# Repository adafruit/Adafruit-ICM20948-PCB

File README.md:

## Adafruit ICM20948 9-DoF IMU PCB

<a href="http://www.adafruit.com/products/4554"><br/>
Click here to purchase one from the Adafruit shop</a>

PCB files for the Adafruit ICM20948 9-DoF IMU. 

Format is EagleCAD schematic and board layout
* https://www.adafruit.com/product/4554

### Description
When you want to sense orientation using inertial measurements, you need an Inertial Measurement Unit, and when it comes to IMUs, the more DoFs, the better! The ICM20948 from Invensense packs 9 Degrees of freedom into a teeny package, making it a one stop shop for all the DOFs you need! Within it’s svelte 3x3mm package there are not just one MEMS sensor die like your common sensors, but two sensor dies! The ICM20948 pair’s Invensense’s MEMS 3-axis accelerometer and gyro with the AK09916 3-axis magnetometer from Asahi Kasei Microdevices Corporation.

 All 9 axes of measurement are made available thanks to a crew of 16-bit Analog to Digital Converters, diligently converting the raw analog signals from the MEMs sensors to digital readings that are accessed via I2C or SPI. Each of the sensors have the quality specs you would expect from such a sensor. Just see what the datasheet has to say:

• 3-Axis Gyroscope with Programmable FSR of ±250 dps, ±500 dps, ±1000 dps, and ±2000 dps

• 3-Axis Accelerometer with Programmable FSR of ±2g, ±4g, ±8g, and ±16g

• 3-Axis Compass with a wide range to ±4900 µT

Now that’s a handy and capable team of sensors, ready to help orient your project in the right direction!

Like any high performance device the ICM20948 can a bit particular about how it needs to be worked with. Unlike the pick and place machines that normally handle these sensors, most of us humans can’t readily take a little guy like the ICM20948 and plop it into our circuit; it’s small! What’s more, the ICM20948 runs on 1.8V which is increasingly common for device manufacturers but isn’t hardly common for makers, learners, prototypers or the like. With that in mind, we’ve put the ICM20948 on a breakout with a 1.8V voltage regulator as well as level shifting circuitry to allow your 3.3V device such as a Feather M4 or Raspberry Pi, or a 5V device such as the Arduino Uno.

To make connections easy, our breakout puts makes the pins of the ICM20948 available on standard 0.100”/ 2.54mm pitch headers for use with a breadboard. Should you wish to avoid soldering, the Stemma QT form factor breakout also includes our Stemma QT connectors which just like the SparkFun Qwiic connectors they’re inspired by (and compatible with). Using these handy connectors you can simply plug in the sensor and get rolling with your project. You can even use them to daisy chain multiple sensors together! All of this is explained with wiring diagrams for use with Arduino or CircuitPython on the pages to come.

Lastly, all the wiring in the world wouldn’t do you much good if you didn’t know how to use those wires to talk to your sensor, so we’ve done the work of writing libraries for Arduino and CircuitPython that will allow you to use the ICM20948 with your favorite development board, be it an Arduino, Feather, Raspberry Pi, or one of the many other Arduino and CircuitPython compatible boards.

### License

Adafruit invests time and resources providing this open source design, please support Adafruit and open-source hardware by purchasing products from [Adafruit](https://www.adafruit.com)!

Designed by Limor Fried/Ladyada for Adafruit Industries.

Creative Commons Attribution/Share-Alike, all text above must be included in any redistribution. 
See license.txt for additional details.

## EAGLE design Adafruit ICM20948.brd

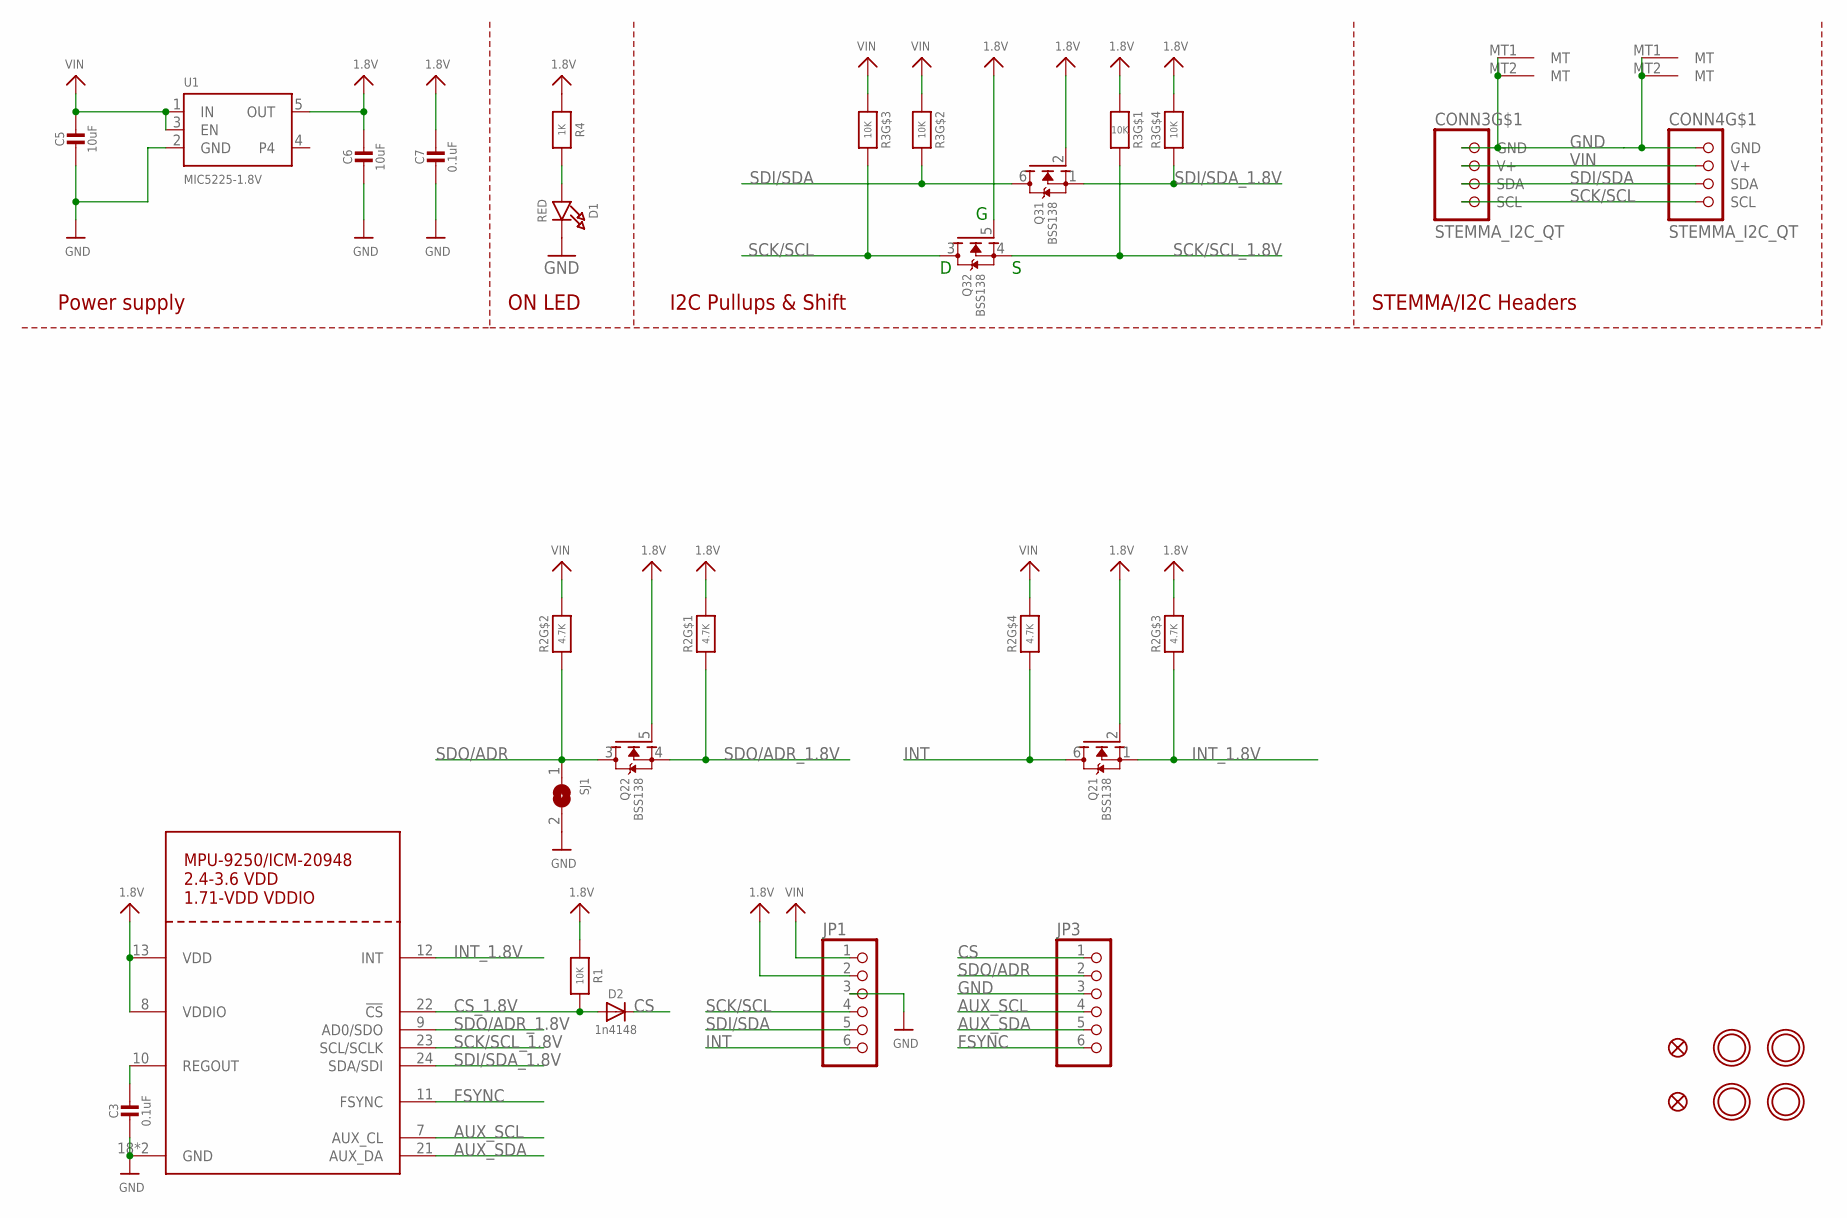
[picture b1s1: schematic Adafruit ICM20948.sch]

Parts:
C3, C7: 0.1uF; 0603-NO
C5, C6: 10uF; 0805-NO
CONN3, CONN4: STEMMA_I2C_QT; JST_SH4
D1: RED; CHIPLED_0603_NOOUTLINE
D2: 1n4148; SOD-323_MINI
FID2, FID4: FIDUCIAL_1MM
JP1, JP3: HEADER-1X670MIL; 1X06_ROUND_70
Q2, Q3: BSS138; SOT363
R1: 10K; 0603-NO
R2: 4.7K; RESPACK_4X0603
R3: 10K; RESPACK_4X0603
R4: 1K; 0603-NO
SJ1: SOLDERJUMPER; SOLDERJUMPER_ARROW_NOPASTE
U1: MIC5225-1.8V; SOT23-5
U$21: MPU-9250_ICM20948; QFN24_3MM_NOEP
U$38, U$39, U$41, U$42: MOUNTINGHOLE2.5; MOUNTINGHOLE_2.5_PLATED

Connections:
1.8V: C6.1, C7.1, JP1.2, Q2.2 (G), Q2.5 (G), Q3.2 (G), Q3.5 (G), R1.1, R2.6 (2), R2.8 (2), R3.4 (1), R3.8 (2), R4.1, U1.5 (OUT), U$21.8 (VDDIO), U$21.13 (VDD)
AUX_SCL: JP3.4, U$21.7 (AUX_CL)
AUX_SDA: JP3.5, U$21.21 (AUX_DA)
CS: D2.C, JP3.1
CS_1.8V: D2.A, R1.2, U$21.22 (!CS)
FSYNC: JP3.6, U$21.11 (FSYNC)
GND: C3.2, C5.2, C6.2, C7.2, CONN3.1 (GND), CONN3.MT1 (MT), CONN3.MT2 (MT), CONN4.1 (GND), CONN4.MT1 (MT), CONN4.MT2 (MT), D1.C, JP1.3, JP3.3, SJ1.2, U1.2 (GND), U$21.18 (GND), U$21.20 (GND)
INT: JP1.6, Q2.6 (D), R2.4 (1)
INT_1.8V: Q2.1 (S), R2.3 (1), U$21.12 (INT)
unnamed: D1.A, R4.2
REGOUT: C3.1, U$21.10 (REGOUT)
SCK/SCL: CONN3.4 (SCL), CONN4.4 (SCL), JP1.4, Q3.3 (D), R3.6 (2)
SCK/SCL_1.8V: Q3.4 (S), R3.1, U$21.23 (SCL/SCLK)
SDI/SDA: CONN3.3 (SDA), CONN4.3 (SDA), JP1.5, Q3.6 (D), R3.7 (2)
SDI/SDA_1.8V: Q3.1 (S), R3.5 (2), U$21.24 (SDA/SDI)
SDO/ADR: JP3.2, Q2.3 (D), R2.2 (1), SJ1.1
SDO/ADR_1.8V: Q2.4 (S), R2.1, U$21.9 (AD0/SDO)
VIN: C5.1, CONN3.2 (V+), CONN4.2 (V+), JP1.1, R2.5 (2), R2.7 (2), R3.2 (1), R3.3 (1), U1.1 (IN), U1.3 (EN)

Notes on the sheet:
I2C Pullups & Shift
STEMMA/I2C Headers
ON LED
Power supply

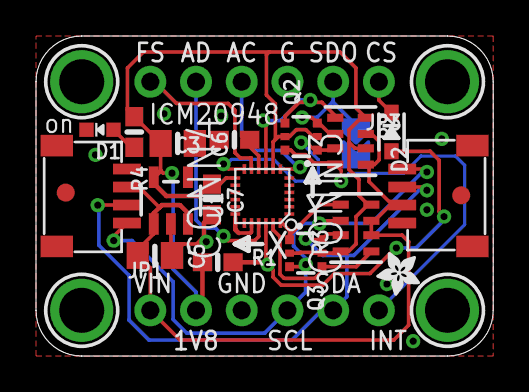
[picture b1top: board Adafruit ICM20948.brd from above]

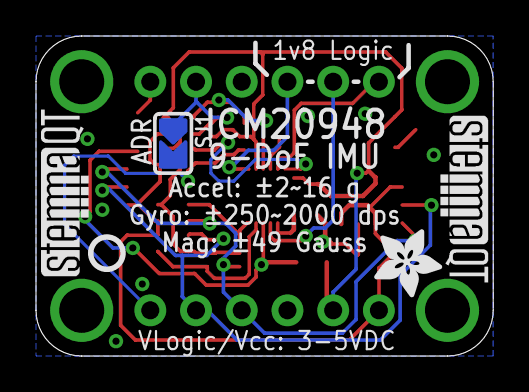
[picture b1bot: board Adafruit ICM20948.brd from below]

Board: 2 copper layers, 25.4 x 17.8 mm, 30 parts (5 on the bottom side), 18 nets.

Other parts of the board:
U$2: ADAFRUIT_2.5MM
U$12: ADAFRUIT_3.5MM
U$45: PCBFEAT-REV-040
U$46, U$47: STEMMAQT

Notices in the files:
parts and their libraries:
microbuilder: This work is placed in the public domain, and may be freely used for commercial and non-commercial work with the following conditions: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
